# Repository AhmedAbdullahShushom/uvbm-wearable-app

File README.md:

# know when to go - microgravity bladder monitoring (Python stack)

```
 patch (BLE/Wi-Fi) -> FastAPI backend -> volume math -> filling-rate ML -> alerts
                          |                                   |
                  Flet mobile app  <---- REST / WebSocket ----> Streamlit dashboard
```

## Layout
| Path | What it does |
|---|---|
| `backend/app/volume.py` | echo time -> wall distance -> ellipsoid volume `V = (pi/6)*L*W*H*cal` |
| `backend/app/predictor.py` | Huber regression filling rate (ml/min), ETA to 60 %, intake heuristic |
| `backend/app/alerts.py` | PREDICTIVE (before 60 %), THRESHOLD (60 %), CRITICAL (80 %) |
| `backend/app/service.py` | pipeline: median smoothing, void detection, prediction, alerting |
| `backend/app/storage.py` | SQLite persistence (state survives restarts) |
| `backend/app/main.py` | REST + WebSocket API |
| `simulator/simulate_patch.py` | fake patch with noise, dropouts, drinking, voids |
| `mobile/` | Flet app, `bleak` BLE gateway, local notifications |
| `web/dashboard.py` | Streamlit dashboard |
| `tests/test_core.py` | unit + end-to-end tests |

## Run
```bash
python -m venv .venv && source .venv/bin/activate
pip install -r requirements.txt

uvicorn backend.app.main:app --reload            # 1. API  (docs at /docs)
python simulator/simulate_patch.py               # 2. simulated patch (1 sim-min per 0.5 s)
streamlit run web/dashboard.py                   # 3. web dashboard
python mobile/app.py                             # 4. mobile app (desktop preview)
pytest -q                                        # tests
```

## Telemetry format (`POST /telemetry`)
```json
{"timestamp":"2026-01-01T10:00:00Z",
 "ap_echo_us":[49.0,151.0], "tr_echo_us":[49.0,170.0], "si_echo_us":[49.0,190.0],
 "signal_quality":0.95, "battery_pct":87}
```
`[front_wall_echo, back_wall_echo]` per axis (AP depth, TR width, SI length), round-trip microseconds.

## Things you MUST do before relying on it
* **Calibrate** `calibration_factor` per user against a reference (catheter or clinical bladder scan).
  Real bladders are not ellipsoids; error of 10-20 % is typical for L x W x H formulas.
* The **intake -> urine heuristic** (`predictor.py`) and the ETA lead time are tunable assumptions,
  not validated physiology. Fit them to your beta-test data.
* Median smoothing delays void detection by ~2-3 frames; voids are timestamped at detection.
* Mobile: Flet has no built-in push API. `plyer` gives local notifications; on Android these mirror to
  a paired watch automatically. Real remote push (FCM) or a dedicated watch UI needs extra work.
* BLE UUIDs / packet layout in `mobile/ble_connector.py` are placeholders for your firmware.
* Research prototype - not a medical device.

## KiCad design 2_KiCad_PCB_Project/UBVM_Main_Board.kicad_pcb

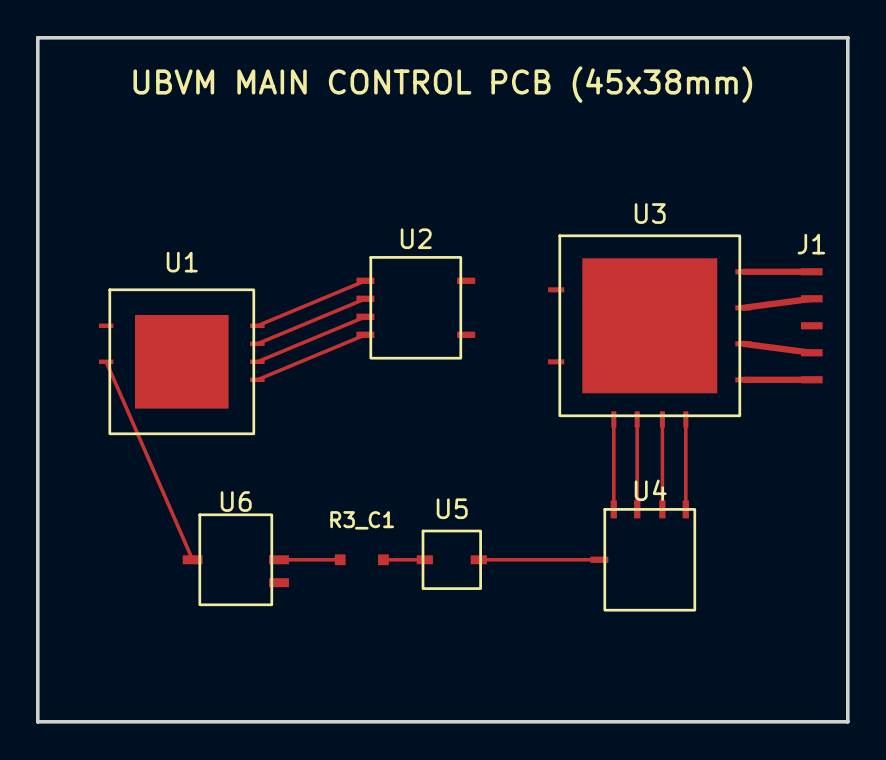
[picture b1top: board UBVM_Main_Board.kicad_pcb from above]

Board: 4 copper layers, 45.0 x 38.0 mm, 8 parts (0 on the bottom side), 17 nets.

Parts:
J1: TO_FLEX_PATCH; J1_FPC_5Pin_Connector
R3_C1: 270R_100pF; RC_Filter_5p88MHz
U1: STM32WB55RG; U1_STM32WB55RG_QFN68
U2: DG409_TX_MUX; U2_DG409_TSSOP16
U3: MAX14808_PULSER; U3_MAX14808_TQFN68
U4: DG408_RX_MUX; U4_DG408_TSSOP16
U5: OPA357; U5_OPA357_SOT23-6
U6: MAX941; U6_MAX941_SOIC8

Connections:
AMP_OUT: R3_C1.1, U5.1
COMP_OUT_TIM_IC: U1.2, U6.7
DINN: U1.4, U2.2
DINP: U1.3, U2.1
GND: J1.3, U1.69, U3.69
LPF_OUT: R3_C1.2, U6.2
LVOUT1: U3.40, U4.1
LVOUT2: U3.41, U4.2
LVOUT3: U3.42, U4.3
LVOUT4: U3.43, U4.4
MUX_RX_OUT: U4.8, U5.3
SEL0: U1.5, U2.3
SEL1: U1.6, U2.4
TX_OUT1: J1.1, U3.20
TX_OUT2: J1.2, U3.21
TX_OUT3: J1.4, U3.22
TX_OUT4: J1.5, U3.23

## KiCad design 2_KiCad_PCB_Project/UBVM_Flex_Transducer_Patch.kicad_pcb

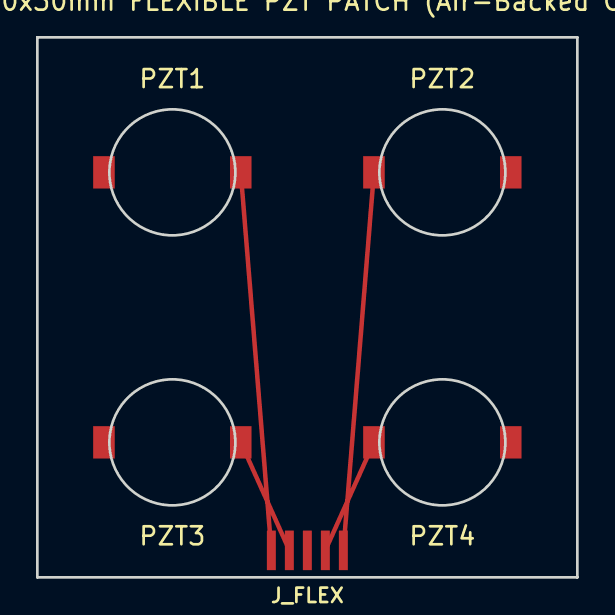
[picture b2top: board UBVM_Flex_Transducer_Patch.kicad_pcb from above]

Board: 2 copper layers, 30.0 x 30.0 mm, 5 parts (0 on the bottom side), 5 nets.

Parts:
J_FLEX: FPC_5Pin_Tail
PZT1: PZT_WrapAround_Pad_Ch1
PZT2: PZT_WrapAround_Pad_Ch2
PZT3: PZT_WrapAround_Pad_Ch3
PZT4: PZT_WrapAround_Pad_Ch4

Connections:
GND: J_FLEX.3, PZT1.2, PZT2.2, PZT3.2, PZT4.2
TX_OUT1: J_FLEX.1, PZT1.1
TX_OUT2: J_FLEX.5, PZT2.1
TX_OUT3: J_FLEX.2, PZT3.1
TX_OUT4: J_FLEX.4, PZT4.1

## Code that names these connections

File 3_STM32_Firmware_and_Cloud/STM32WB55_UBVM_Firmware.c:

/**
 * @file    STM32WB55_UBVM_Firmware.c
 * @brief   Complete Firmware Architecture for the UBVM Microcontroller (STM32WB55RG)
 *          Implements:
 *            1. TIM1 Complementary PWM Burst Generator: 5 pulses @ 2 MHz (3.3V) on DINP (PA8) & DINN (PB13)
 *               with 180-degree phase shift triggered every 2.5 seconds.
 *            2. GPIO Multiplexer Addressing (SEL0 = PC0, SEL1 = PC1) for DG409 (Tx) and DG408 (Rx)
 *               stepping across Channels 1-4 at 10-second intervals.
 *            3. TIM2 Input Capture + DMA (PA0): Logs rising-edge timestamps from MAX941 comparator output
 *               with 15.6 ns resolution (64 MHz timer clock) and zero CPU overhead.
 *            4. BLE GATT Server Notification: Transmits [Channel_ID, Timestamp_Array] to Mobile App.
 */

#include "stm32wbxx_hal.h"
#include <stdint.h>
#include <string.h>

#define NUM_TRANSDUCERS         4
#define MAX_ECHO_TIMESTAMPS     32
#define BLANKING_WINDOW_TICKS   1280  /* 20 us blind zone @ 64 MHz to ignore Tx excitation ringdown */

TIM_HandleTypeDef htim1;  /* 2 MHz 5-Pulse Complementary Burst Timer (DINP / DINN) */
TIM_HandleTypeDef htim2;  /* 64 MHz Input Capture Timer for MAX941 Comparator Output */
DMA_HandleTypeDef hdma_tim2_ch1;

uint32_t dma_capture_buffer[MAX_ECHO_TIMESTAMPS];
uint8_t  active_channel = 0; /* 0 to 3 corresponding to Transducers 1 to 4 */

typedef struct __attribute__((packed)) {
    uint8_t  transducer_id;          /* 1 to 4 */
    uint16_t anterior_echo_us_x100;  /* Anterior wall ToF in 0.01 us units */
    uint16_t posterior_echo_us_x100; /* Posterior wall ToF in 0.01 us units */
} UBVM_BLE_Packet_t;

/**
 * @brief Select active ultrasonic transducer (1-4) via DG409 & DG408 SEL0/SEL1 pins
 */
void UBVM_Select_Transducer_Channel(uint8_t ch_index) {
    HAL_GPIO_WritePin(GPIOC, GPIO_PIN_0, (ch_index & 0x01) ? GPIO_PIN_SET : GPIO_PIN_RESET); /* SEL0 */
    HAL_GPIO_WritePin(GPIOC, GPIO_PIN_1, (ch_index & 0x02) ? GPIO_PIN_SET : GPIO_PIN_RESET); /* SEL1 */
}

/**
 * @brief Configure TIM1 for 2 MHz One-Pulse Burst Mode with Repetition Counter = 4 (5 pulses total)
 *        System Clock = 64 MHz -> Period (ARR) = 31 (64 MHz / 32 = 2.00 MHz), Pulse (CCR1) = 16 (50% duty)
 */
void UBVM_TIM1_2MHz_Burst_Init(void) {
    TIM_OC_InitTypeDef sConfigOC = {0};
    TIM_BreakDeadTimeConfigTypeDef sBreakDeadTimeConfig = {0};

    htim1.Instance = TIM1;
    htim1.Init.Prescaler = 0;
    htim1.Init.CounterMode = TIM_COUNTERMODE_UP;
    htim1.Init.Period = 31;                /* 64 MHz / (31 + 1) = 2.0 MHz */
    htim1.Init.ClockDivision = TIM_CLOCKDIVISION_DIV1;
    htim1.Init.RepetitionCounter = 4;      /* RCR = 4 -> Exactly 5 pulses per trigger! */
    htim1.Init.AutoReloadPreload = TIM_AUTORELOAD_PRELOAD_DISABLE;
    HAL_TIM_PWM_Init(&htim1);
    HAL_TIM_OnePulse_Init(&htim1, TIM_OPMODE_SINGLE);

    sConfigOC.OCMode = TIM_OCMODE_PWM1;
    sConfigOC.Pulse = 16;                  /* 50% Duty Cycle (250 ns HIGH, 250 ns LOW) */
    sConfigOC.OCPolarity = TIM_OCPOLARITY_HIGH;
    sConfigOC.OCNPolarity = TIM_OCNPOLARITY_HIGH; /* Complementary output 180 deg out of phase */
    sConfigOC.OCFastMode = TIM_OCFAST_DISABLE;
    HAL_TIM_PWM_ConfigChannel(&htim1, &sConfigOC, TIM_CHANNEL_1);

    sBreakDeadTimeConfig.DeadTime = 0;
    sBreakDeadTimeConfig.BreakState = TIM_BREAK_DISABLE;
    sBreakDeadTimeConfig.AutomaticOutput = TIM_AUTOMATICOUTPUT_ENABLE;
    HAL_TIMEx_ConfigBreakDeadTime(&htim1, &sBreakDeadTimeConfig);
}

/**
 * @brief Configure TIM2 Channel 1 (PA0) in Input Capture Mode with DMA to capture MAX941 rising edges
 */
void UBVM_TIM2_InputCapture_DMA_Init(void) {
    TIM_IC_InitTypeDef sConfigIC = {0};

    htim2.Instance = TIM2;
    htim2.Init.Prescaler = 0;              /* 64 MHz tick rate (15.625 ns resolution) */
    htim2.Init.CounterMode = TIM_COUNTERMODE_UP;
    htim2.Init.Period = 0xFFFFFFFF;
    htim2.Init.ClockDivision = TIM_CLOCKDIVISION_DIV1;
    HAL_TIM_IC_Init(&htim2);

    sConfigIC.ICPolarity = TIM_INPUTCHANNELPOLARITY_RISING;
    sConfigIC.ICSelection = TIM_ICSELECTION_DIRECTTI;
    sConfigIC.ICPrescaler = TIM_ICPSC_DIV1;
    sConfigIC.ICFilter = 0;
    HAL_TIM_IC_ConfigChannel(&htim2, &sConfigIC, TIM_CHANNEL_1);
}

/**
 * @brief Execute one complete Pulse-Echo measurement cycle on the currently selected transducer
 */
void UBVM_Execute_Pulse_Echo_Measurement(UBVM_BLE_Packet_t *out_packet) {
    memset(dma_capture_buffer, 0, sizeof(dma_capture_buffer));

    /* 1. Reset & Start TIM2 Input Capture DMA before firing ultrasonic burst */
    __HAL_TIM_SET_COUNTER(&htim2, 0);
    HAL_TIM_IC_Start_DMA(&htim2, TIM_CHANNEL_1, dma_capture_buffer, MAX_ECHO_TIMESTAMPS);

    /* 2. Fire 5-Cycle 2 MHz Complementary Burst on DINP (TIM1_CH1) and DINN (TIM1_CH1N) */
    HAL_TIM_PWM_Start(&htim1, TIM_CHANNEL_1);
    HAL_TIMEx_PWMN_Start(&htim1, TIM_CHANNEL_1);

    /* 3. Wait 200 microseconds for Anterior & Posterior bladder wall echoes to return */
    for (volatile int delay = 0; delay < 3200; delay++) { __NOP(); }

    /* 4. Stop DMA and average Anterior (< 70 us) and Posterior (>= 70 us) echo timestamps */
    HAL_TIM_IC_Stop_DMA(&htim2, TIM_CHANNEL_1);

    uint32_t ant_sum = 0, ant_cnt = 0;
    uint32_t post_sum = 0, post_cnt = 0;
    const uint32_t mid_split_ticks = 70 * 64; /* 70 us boundary @ 64 MHz */

    for (int i = 0; i < MAX_ECHO_TIMESTAMPS; i++) {
        uint32_t ticks = dma_capture_buffer[i];
        if (ticks > BLANKING_WINDOW_TICKS) {
            if (ticks < mid_split_ticks) {
                ant_sum += ticks;
                ant_cnt++;
            } else if (ticks < (160 * 64)) {
                post_sum += ticks;
                post_cnt++;
            }
        }
    }

    out_packet->transducer_id = active_channel + 1;
    out_packet->anterior_echo_us_x100  = (ant_cnt > 0)  ? (uint16_t)(((ant_sum / ant_cnt) * 100) / 64)   : 0;
    out_packet->posterior_echo_us_x100 = (post_cnt > 0) ? (uint16_t)(((post_sum / post_cnt) * 100) / 64) : 0;
}
